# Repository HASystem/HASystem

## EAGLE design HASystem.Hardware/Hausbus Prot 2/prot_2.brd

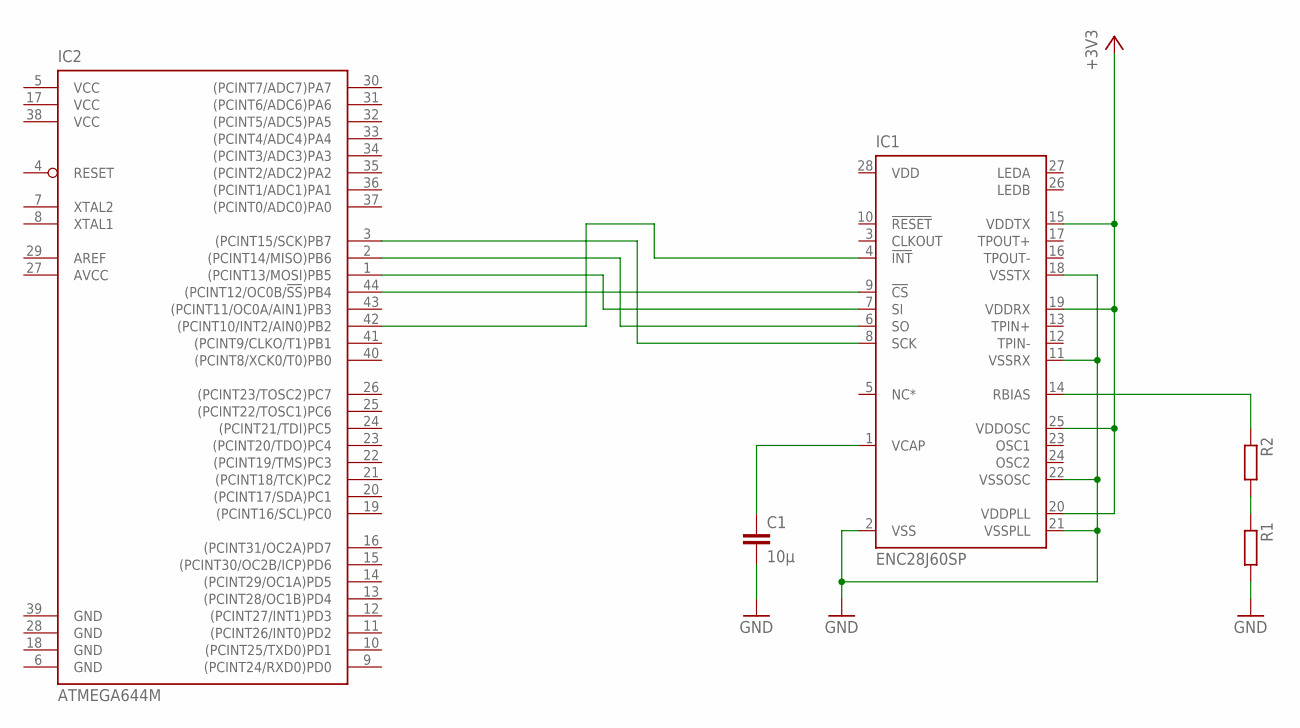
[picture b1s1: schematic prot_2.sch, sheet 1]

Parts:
C1: 10µ; C1206K
IC1: ENC28J60SP; DIL28-3
IC2: ATMEGA644M; QFN44ML8X8
R1, R2: R-EU_R1206; R1206

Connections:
+3V3: IC1.15 (VDDTX), IC1.19 (VDDRX), IC1.20 (VDDPLL), IC1.25 (VDDOSC); also elsewhere on the board
AVCC: IC2.27 (AVCC)
GND: C1.2, IC1.2 (VSS), IC1.11 (VSSRX), IC1.18 (VSSTX), IC1.21 (VSSPLL), IC1.22 (VSSOSC), IC2.6 (GND), IC2.18 (GND), IC2.28 (GND), IC2.39 (GND), R1.2; also elsewhere on the board
unnamed: IC1.9 (!CS), IC2.44 ((PCINT12/OC0B/!SS!)PB4)
unnamed: IC1.7 (SI), IC2.1 ((PCINT13/MOSI)PB5)
unnamed: IC1.6 (SO), IC2.2 ((PCINT14/MISO)PB6)
unnamed: IC1.8 (SCK), IC2.3 ((PCINT15/SCK)PB7)
unnamed: IC1.4 (!INT), IC2.42 ((PCINT10/INT2/AIN0)PB2)
unnamed: C1.1, IC1.1 (VCAP)
unnamed: R1.1, R2.2
unnamed: IC1.14 (RBIAS), R2.1
VCC: IC2.5 (VCC), IC2.17 (VCC), IC2.38 (VCC); also elsewhere on the board

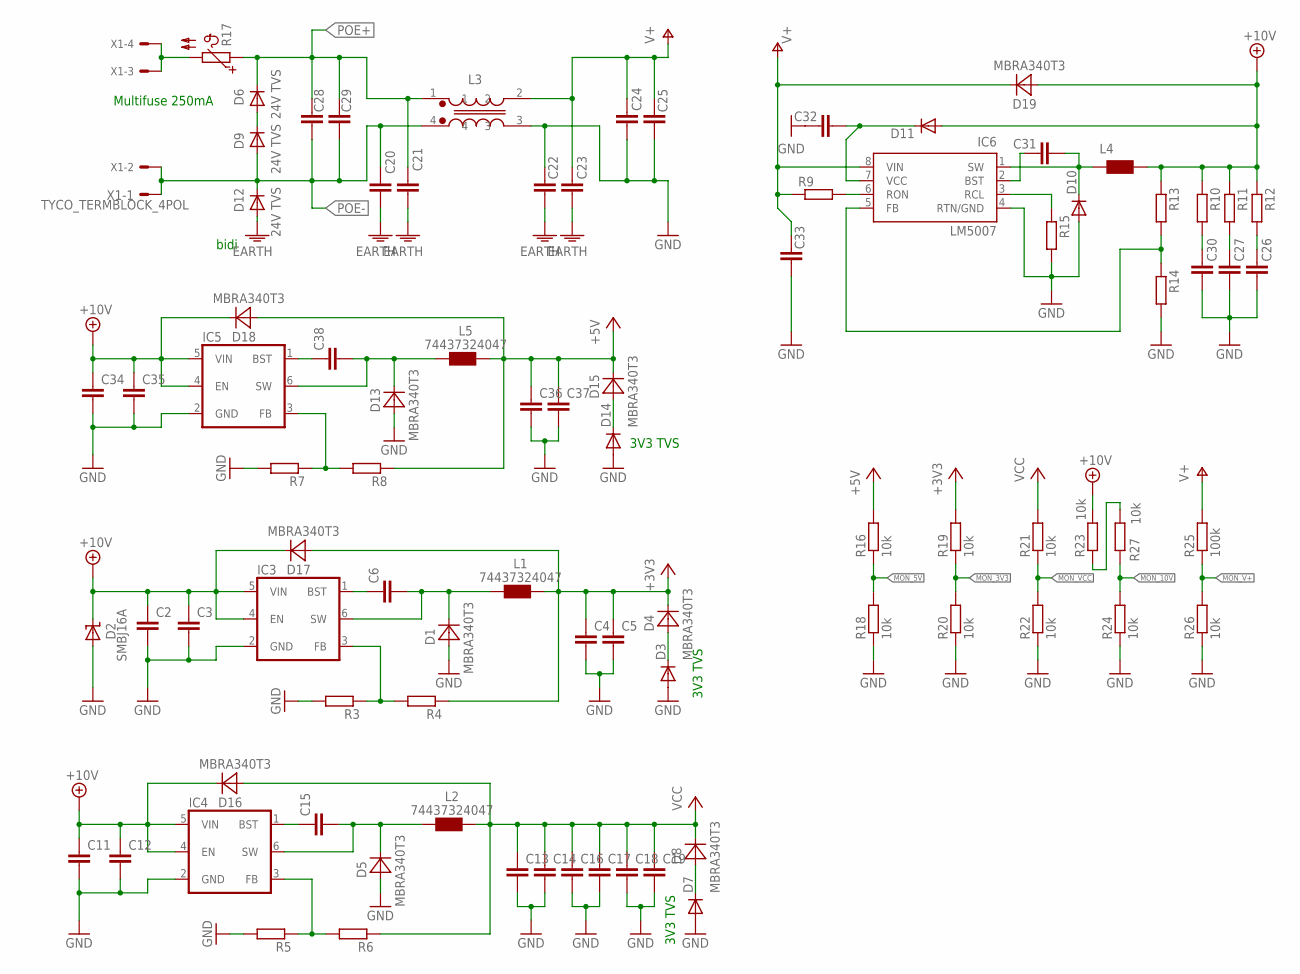
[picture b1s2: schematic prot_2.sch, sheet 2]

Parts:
C2, C3, C4, C5, C6, C11, C12, C13, C14, C15, C16, C17, C18, C19, C20, C21, C22, C23, C24, C25, C26, C27, C28, C29, C30, C31, C32, C33, C34, C35, C36, C37, C38: C-EUC1206; C1206
D1, D4, D5, D8, D13, D15, D16, D17, D18, D19: MBRA340T3; SMA
D2: SMBJ16A; DO214AA_POL
D3, D7, D14: DIODE-DO214AA; DO214AA
D6, D9, D12: 24V TVS; SMC
D10, D11: DIODE-SOD123; SOD123
IC3, IC4, IC5: ADP2301; TSOT-6
IC6: LM5007; SOP-08
L1, L2, L5: 74437324047; WüRTH_4020
L3: WE-SL5
L4: SRU1048
R3, R4, R5, R6, R7, R8, R9, R10, R11, R12, R13, R14, R15: R-EU_R0603; R0603
R16, R18, R19, R20, R21, R22, R23, R24, R26, R27: 10k; R0603
R17: B59773; B773
R25: 100k; R0603
X1: TYCO_TERMBLOCK_4POL; TYPO_TERMBLOCK_4POL

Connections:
+3V3: C4.1, C5.1, D4.C, D17.A, L1.P$2 (2), R4.1, R19.2; also elsewhere on the board
+5V: C36.1, C37.1, D15.C, D18.A, L5.P$2 (2), R8.1, R16.2
+10V: C2.1, C3.1, C11.1, C12.1, C34.1, C35.1, D2.C, D11.A, D16.C, D17.C, D18.C, D19.A, IC3.4 (EN), IC3.5 (VIN), IC4.4 (EN), IC4.5 (VIN), IC5.4 (EN), IC5.5 (VIN), L4.2, R10.1, R11.1, R12.1, R13.1, R23.2
EARTH: C20.2, C21.2, C22.2, C23.2, D12.A
GND: C2.2, C3.2, C4.2, C5.2, C11.2, C12.2, C13.2, C14.2, C16.2, C17.2, C18.2, C19.2, C22.1, C24.2, C25.2, C26.2, C27.2, C30.2, C32.1, C33.2, C34.2, C35.2, C36.2, C37.2, D1.A, D2.A, D3.A, D5.A, D7.A, D10.A, D13.A, D14.A, IC3.2 (GND), IC4.2 (GND), IC5.2 (GND), IC6.4 (RTN/GND), L3.3, R3.2, R5.2, R7.2, R15.2, R18.1, R20.1, R22.1, R24.1, R26.1; also elsewhere on the board
MON_3V3: R19.1, R20.2
MON_5V: R16.1, R18.2
MON_10V: R24.2, R27.1
MON_V+: R25.1, R26.2
MON_VCC: R21.1, R22.2
unnamed: C6.2, D1.C, IC3.6 (SW), L1.P$1 (1)
unnamed: D3.C, D4.A
unnamed: C6.1, IC3.1 (BST)
unnamed: D6.A, D9.C
unnamed: R23.1, R27.2
unnamed: C15.2, D5.C, IC4.6 (SW), L2.P$1 (1)
unnamed: IC3.3 (FB), R3.1, R4.2
unnamed: C15.1, IC4.1 (BST)
unnamed: IC4.3 (FB), R5.1, R6.2
unnamed: D7.C, D8.A
unnamed: IC6.3 (RCL), R15.1
unnamed: C31.2, D10.C, IC6.1 (SW), L4.1
unnamed: C31.1, IC6.2 (BST)
unnamed: R17.P$2 (2), X1.3 (MS), X1.4 (MS)
unnamed: IC6.5 (FB), R13.2, R14.1
unnamed: C30.1, R10.2
unnamed: C27.1, R11.2
unnamed: C26.1, R12.2
unnamed: C38.2, D13.C, IC5.6 (SW), L5.P$1 (1)
unnamed: IC6.6 (RON), R9.2
unnamed: C38.1, IC5.1 (BST)
unnamed: IC5.3 (FB), R7.1, R8.2
unnamed: D14.C, D15.A
unnamed: C32.2, D11.C, IC6.7 (VCC)
POE+: C21.1, C28.1, C29.1, D6.C, L3.1, R17.P$1 (1); also elsewhere on the board
POE-: C20.1, C28.2, C29.2, D9.A, D12.C, L3.4, X1.1 (S), X1.2 (MS); also elsewhere on the board
V+: C23.1, C24.1, C25.1, C33.1, D19.C, IC6.8 (VIN), L3.2, R9.1, R25.2
VCC: C13.1, C14.1, C16.1, C17.1, C18.1, C19.1, D8.C, D16.A, L2.P$2 (2), R6.1, R21.2; also elsewhere on the board

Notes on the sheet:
3V3 TVS
bidi
Multifuse 250mA

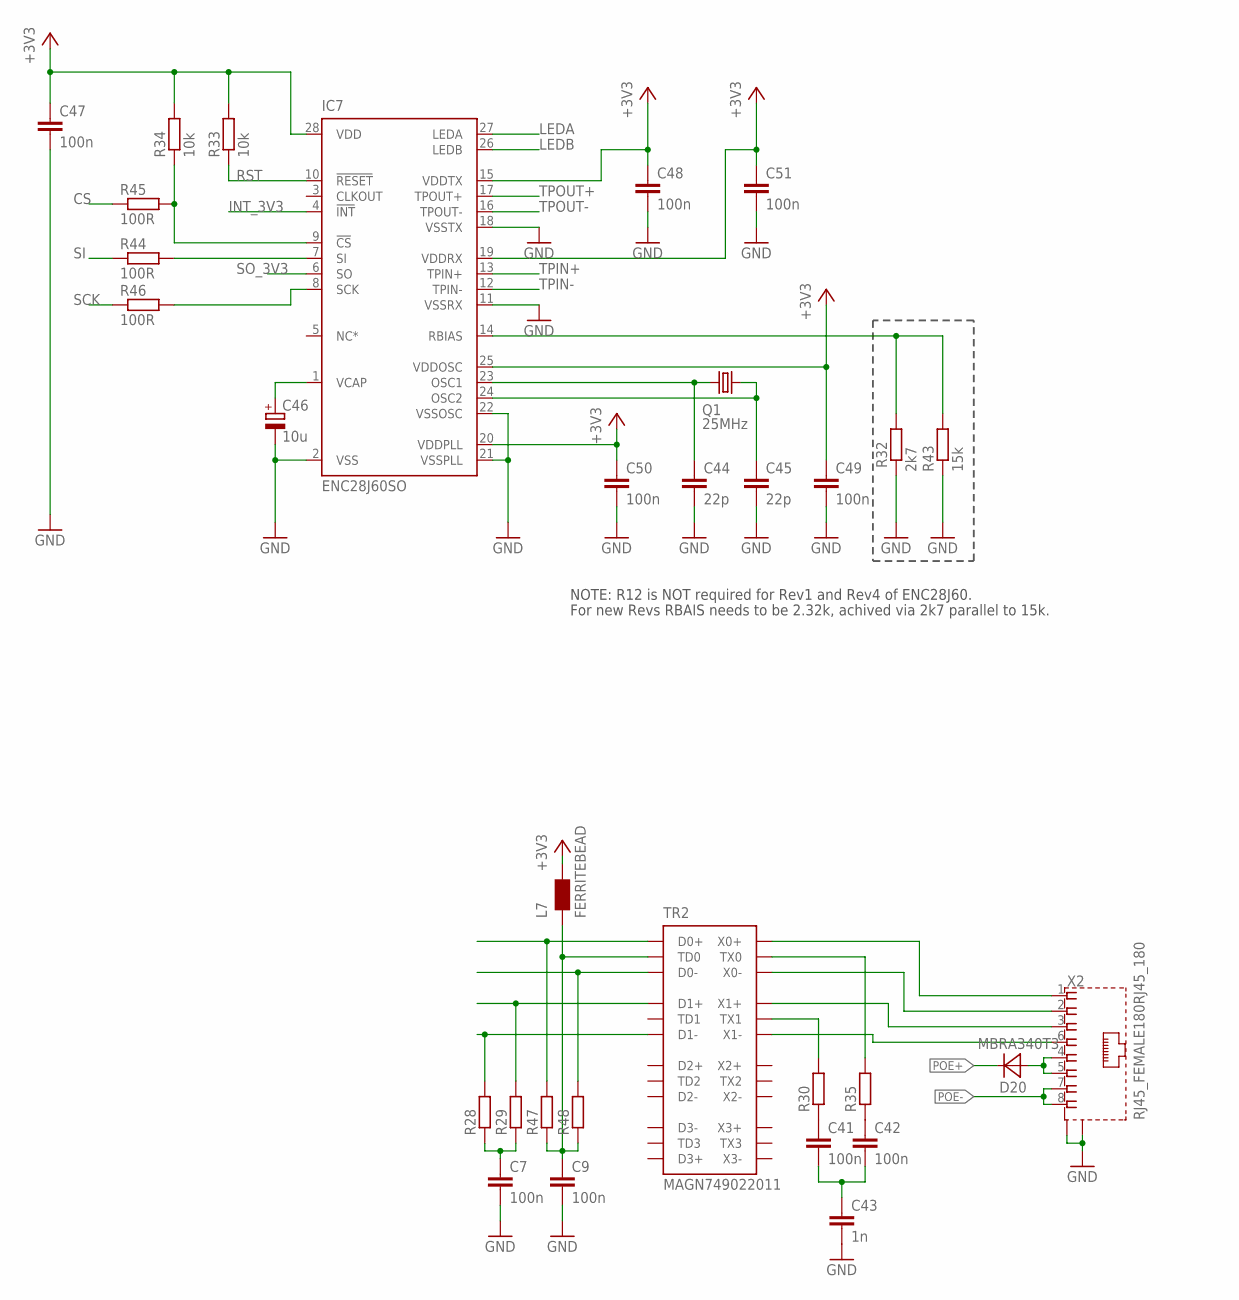
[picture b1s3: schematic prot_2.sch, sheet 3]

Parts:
C7, C9, C41, C42: 100n; C0603
C43: 1n; C0603
C44, C45: 22p; C1206
C46: 10u; E2,5-5
C47, C48, C49, C50, C51: 100n; C1206
D20: MBRA340T3; SMA
IC7: ENC28J60SO; SO28W
L7: FERRITEBEAD; R0603
Q1: 25MHz; HC49/S
R28, R29, R47, R48: R-EU_R0603; R0603
R30, R35: R-EU_MELF0207W; MINI_MELF-0207W
R32: 2k7; M1206
R33, R34: 10k; M1206
R43: 15k; M1206
R44, R45, R46: 100R; M1206
TR2: MAGN749022011; SO24_XL
X2: RJ45_FEMALE180RJ45_180; RJ45-SHIELD180

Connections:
+3V3: C47.1, C48.1, C49.1, C50.1, C51.1, IC7.15 (VDDTX), IC7.19 (VDDRX), IC7.20 (VDDPLL), IC7.25 (VDDOSC), IC7.28 (VDD), L7.2, R33.2, R34.2; also elsewhere on the board
CS: R45.2
GND: C7.2, C9.2, C43.2, C44.2, C45.2, C46.-, C47.2, C48.2, C49.2, C50.2, C51.2, IC7.2 (VSS), IC7.11 (VSSRX), IC7.18 (VSSTX), IC7.21 (VSSPLL), IC7.22 (VSSOSC), R32.2, R43.2, X2.S1 (S), X2.S2 (S); also elsewhere on the board
INT_3V3: IC7.4 (!INT)
LEDA: IC7.27 (LEDA)
LEDB: IC7.26 (LEDB)
unnamed: C44.1, IC7.23 (OSC1), Q1.1
unnamed: C45.1, IC7.24 (OSC2), Q1.2
unnamed: C46.+, IC7.1 (VCAP)
unnamed: IC7.14 (RBIAS), R32.1, R43.1
unnamed: C41.1, R30.1
unnamed: C9.1, L7.1, R47.1, R48.1, TR2.P$1 (TD0)
unnamed: IC7.7 (SI), R44.1
unnamed: IC7.9 (!CS), R34.1, R45.1
unnamed: TR2.P$23 (X0+), X2.1
unnamed: TR2.P$22 (X0-), X2.2
unnamed: TR2.P$20 (X1+), X2.3
unnamed: TR2.P$19 (X1-), X2.6
unnamed: C41.2, C42.2, C43.1
unnamed: R28.2, TR2.P$6 (D1-)
unnamed: C7.1, R28.1, R29.1
unnamed: R29.2, TR2.P$5 (D1+)
unnamed: R35.2, TR2.P$24 (TX0)
unnamed: C42.1, R35.1
unnamed: D20.A, X2.4, X2.5
unnamed: R48.2, TR2.P$3 (D0-)
unnamed: R30.2, TR2.P$21 (TX1)
unnamed: R47.2, TR2.P$2 (D0+)
unnamed: IC7.8 (SCK), R46.1
POE+: D20.C; also elsewhere on the board
POE-: X2.7, X2.8; also elsewhere on the board
RST: IC7.10 (!RESET), R33.1
SCK: R46.2
SI: R44.2
SO_3V3: IC7.6 (SO)
TPIN+: IC7.13 (TPIN+)
TPIN-: IC7.12 (TPIN-)
TPOUT+: IC7.17 (TPOUT+)
TPOUT-: IC7.16 (TPOUT-)

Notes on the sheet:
NOTE: R12 is NOT required for Rev1 and Rev4 of ENC28J60.
For new Revs RBAIS needs to be 2.32k, achived via 2k7 parallel to 15k.

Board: 2 copper layers, 124 parts (0 on the bottom side), 70 nets, no tracks yet.

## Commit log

2015-01-03 first checkin
2015-01-10 add datasheet for ethernet controller ENC28J60
2015-01-12 working ethernet
2015-02-23 initialize commit
2015-02-23 again
2015-02-23 init embedded project
2015-02-23 fix embedded project
2015-02-23 initialized desktop application
2015-02-25 fixed problems with mef
2015-02-25 added logic for notify property changed
2015-02-25 added delegate command
2015-02-25 cleanup
2015-02-25 Add gitignores to avoid commiting trash
2015-02-25 add basic service structure
2015-02-25 add missing file
2015-02-26 change output directory
2015-03-23 fixed fcpu to 16MHz
2015-03-23 added protoype for gpio
2015-04-13 add adc stub add utils refactor names
2015-04-13 use typedefs allow printutils without args adc copy-past fixes
2015-04-13 Init gates.
2015-04-27 Added first restful service
2015-04-27 wip networkstack arp
2015-06-08 Added dhcp server stuff
2015-06-08 Moved the DHCP stuff to the server project
2015-06-12 using radigs network stack
2015-07-12 own project for wcf remote endpoint
2015-07-12 refactor dhcp to use ipaddress dynamic service detection add basic server infrastrcture
2015-07-16 bad working solution
2015-07-16 improved solution
2015-07-25 working on service improved logic
2015-07-27 autodetect devices by dhcp wip on components
2015-07-27 wip on component service
2015-07-27 Added gui stuff for the gates.
2015-07-27 new ValueType system
2015-07-28 component service component crud and stub to get value
2015-07-30 refactor linq statements to avoid "where"
2015-08-10 Grafic stuff.
2015-08-10 Removed unused stuff.
2015-08-10 house as instance
2015-08-10 Added first component.
2015-08-10 Removed obsolete code.
2015-08-10 Schemetic and Layout of Prot 2.
2015-08-10 wip on house service
2015-08-10 shared project for wcf data- & service-contracts
2015-08-12 Moved canvas to a own control for drag drop.
2015-08-12 Added a dragdrop helper.
2015-08-13 Tried drag drop stuff.
2015-08-14 Added stackpanel with controls.
2015-08-15 Added drag drop container.
2015-08-15 Added ribbon.
2015-08-15 Enhanced ribbon.
2015-08-15 Added some logic for later use,
2015-08-15 Added csproj.
2015-08-16 make components house specific load wcf-services dynamic
2015-08-16 central mapping init

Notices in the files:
parts and their libraries:
EagleLibrary_Wuerth_Elektronik_eiSos_V6_: Copyright: Würth Elektronik
